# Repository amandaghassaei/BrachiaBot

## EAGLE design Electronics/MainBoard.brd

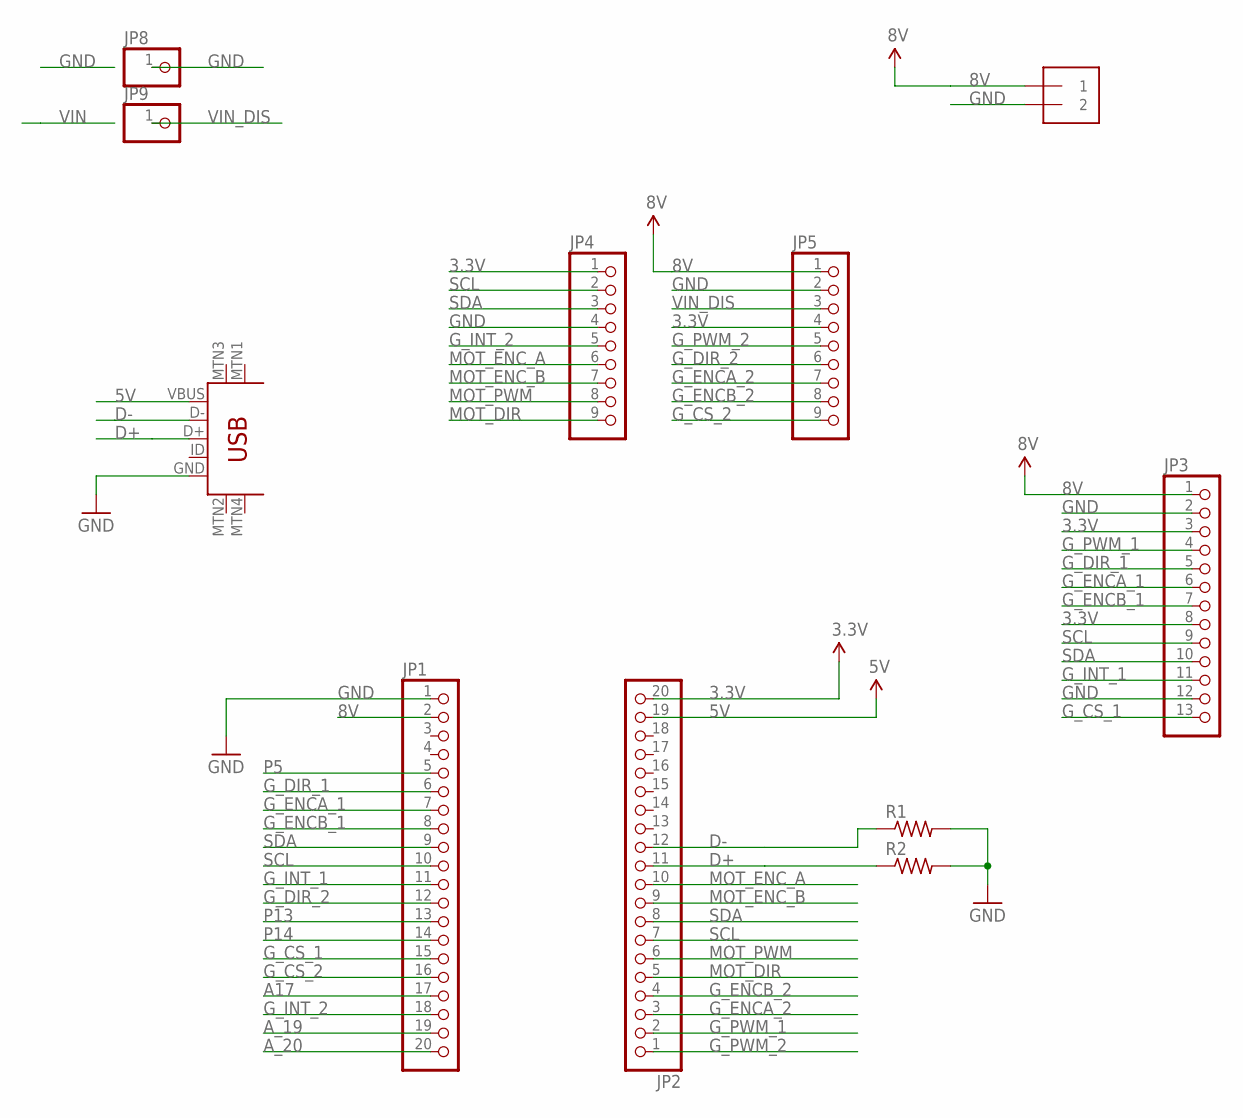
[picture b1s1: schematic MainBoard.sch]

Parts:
J1: 1X2-3.5MM
JP1, JP2: PINHD-1X20; 1X20
JP3: PINHD-1X13; 1X13
JP4, JP5: PINHD-1X9; 1X09-BIG
JP8, JP9: PINHD-1X1; 1X01
R1, R2: RES-US1206; R1206
U$1: USB-MINIB-5PIN; USB-MINIB

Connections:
3.3V: JP2.20, JP3.3, JP3.8, JP4.1, JP5.4
5V: JP2.19, U$1.VBUS
8V: J1.1, JP1.2, JP3.1, JP5.1
A17: JP1.17
A_19: JP1.19
A_20: JP1.20
D+: JP2.11, R2.1, U$1.D+
D-: JP2.12, R1.1, U$1.D-
GND: J1.2, JP1.1, JP3.2, JP3.12, JP4.4, JP5.2, JP8.1, R1.2, R2.2, U$1.GND
G_CS_1: JP1.15, JP3.13
G_CS_2: JP1.16, JP5.9
G_DIR_1: JP1.6, JP3.5
G_DIR_2: JP1.12, JP5.6
G_ENCA_1: JP1.7, JP3.6
G_ENCA_2: JP2.3, JP5.7
G_ENCB_1: JP1.8, JP3.7
G_ENCB_2: JP2.4, JP5.8
G_INT_1: JP1.11, JP3.11
G_INT_2: JP1.18, JP4.5
G_PWM_1: JP2.2, JP3.4
G_PWM_2: JP2.1, JP5.5
MOT_DIR: JP2.5, JP4.9
MOT_ENC_A: JP2.10, JP4.6
MOT_ENC_B: JP2.9, JP4.7
MOT_PWM: JP2.6, JP4.8
P5: JP1.5
P13: JP1.13
P14: JP1.14
SCL: JP1.10, JP2.7, JP3.9, JP4.2
SDA: JP1.9, JP2.8, JP3.10, JP4.3
VIN_DIS: JP5.3, JP9.1

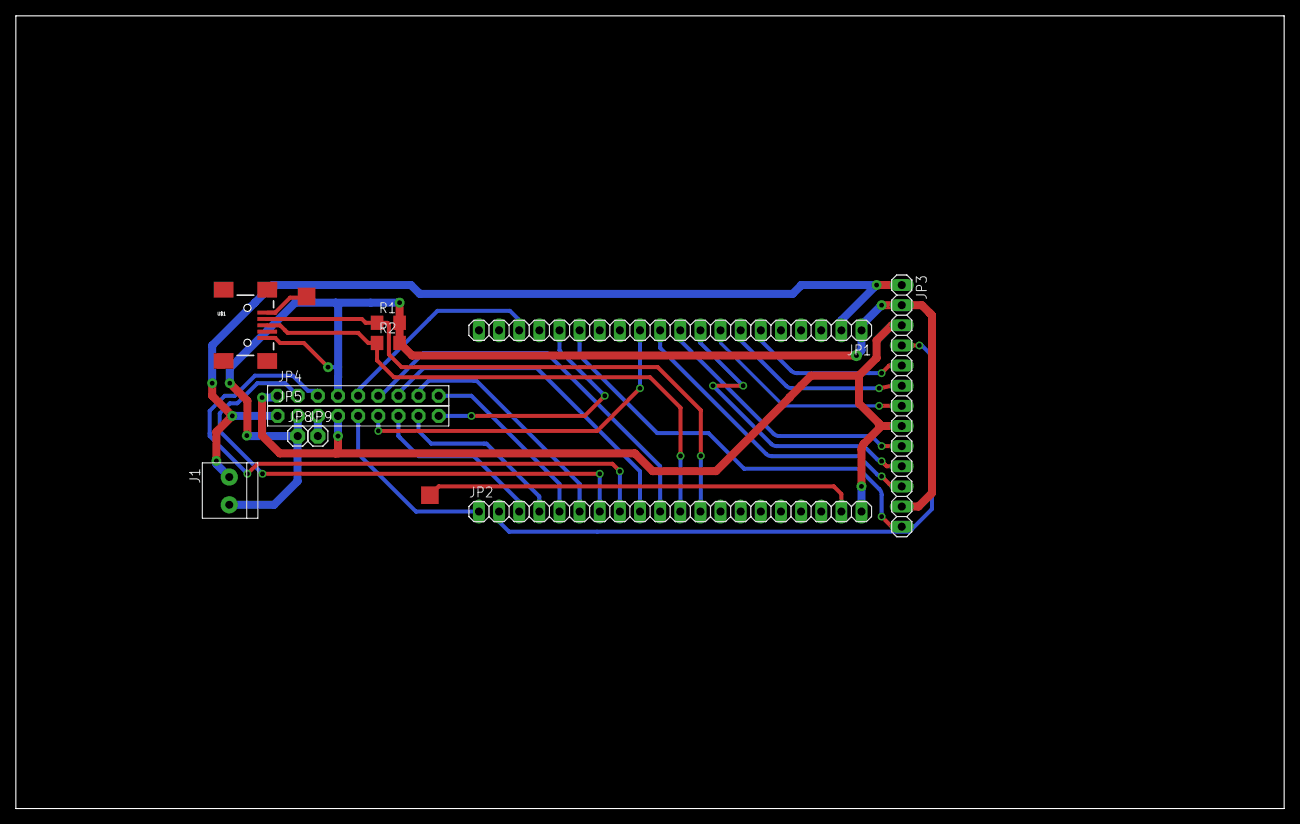
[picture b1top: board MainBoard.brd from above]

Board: 2 copper layers, 160.0 x 100.0 mm, 11 parts (0 on the bottom side), 25 nets.

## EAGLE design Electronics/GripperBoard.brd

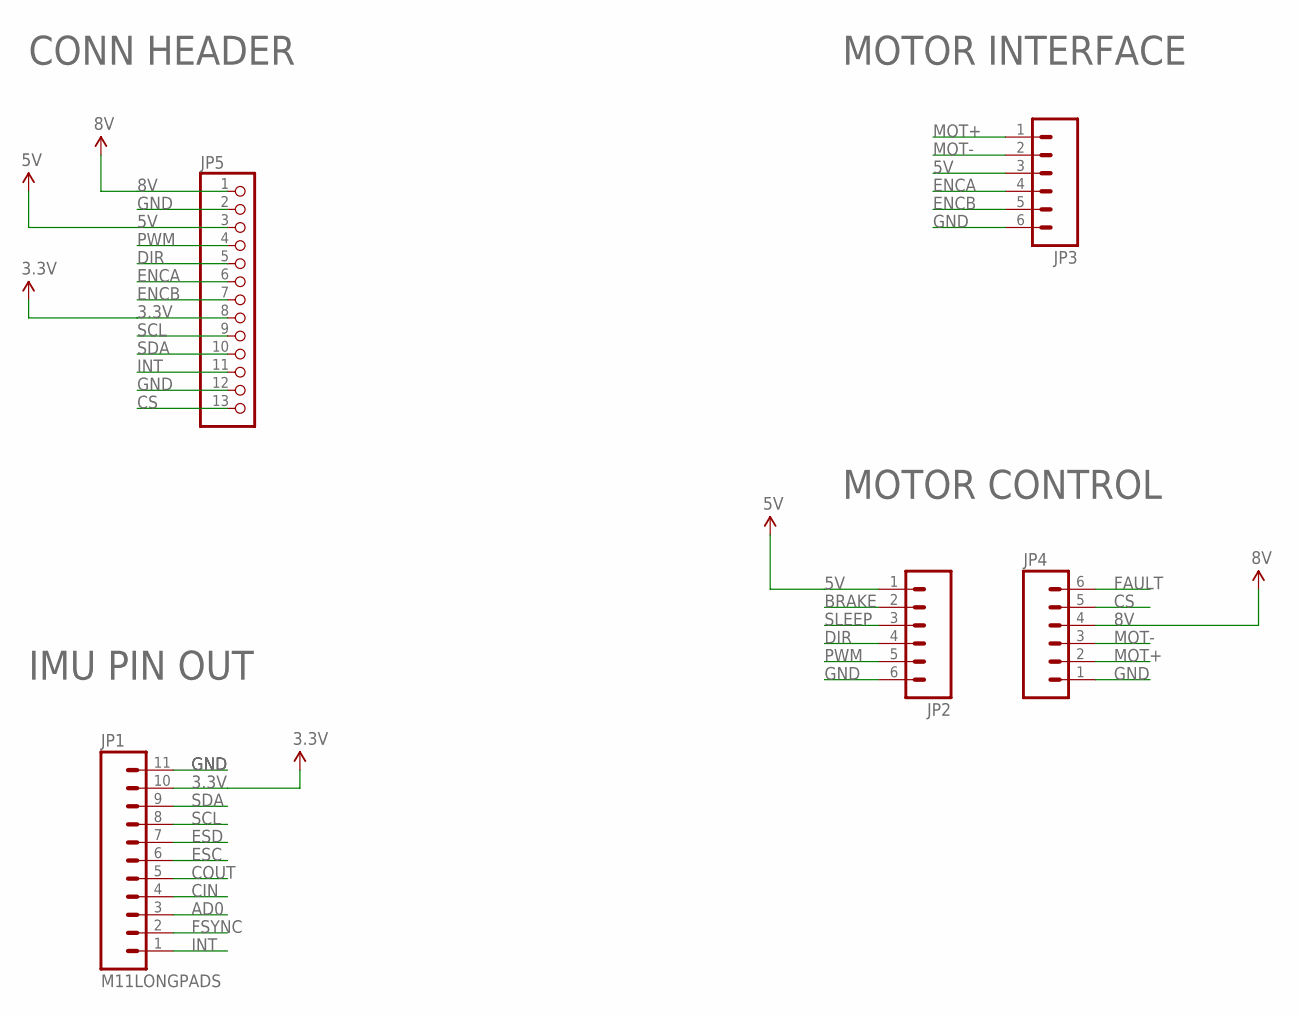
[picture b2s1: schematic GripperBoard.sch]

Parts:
JP1: M11LONGPADS; 1X11_LONGPADS
JP2, JP3, JP4: M06LONGPADS; 1X06_LONGPADS
JP5: PINHD-1X13; 1X13

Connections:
3.3V: JP1.10, JP5.8
5V: JP2.1, JP3.3, JP5.3
8V: JP4.4, JP5.1
AD0: JP1.3
BRAKE: JP2.2
CIN: JP1.4
COUT: JP1.5
CS: JP4.5, JP5.13
DIR: JP2.4, JP5.5
ENCA: JP3.4, JP5.6
ENCB: JP3.5, JP5.7
ESC: JP1.6
ESD: JP1.7
FAULT: JP4.6
FSYNC: JP1.2
GND: JP1.11, JP2.6, JP3.6, JP4.1, JP5.2, JP5.12
INT: JP1.1, JP5.11
MOT+: JP3.1, JP4.2
MOT-: JP3.2, JP4.3
PWM: JP2.5, JP5.4
SCL: JP1.8, JP5.9
SDA: JP1.9, JP5.10
SLEEP: JP2.3

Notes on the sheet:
MOTOR CONTROL
MOTOR INTERFACE
IMU PIN OUT
CONN HEADER

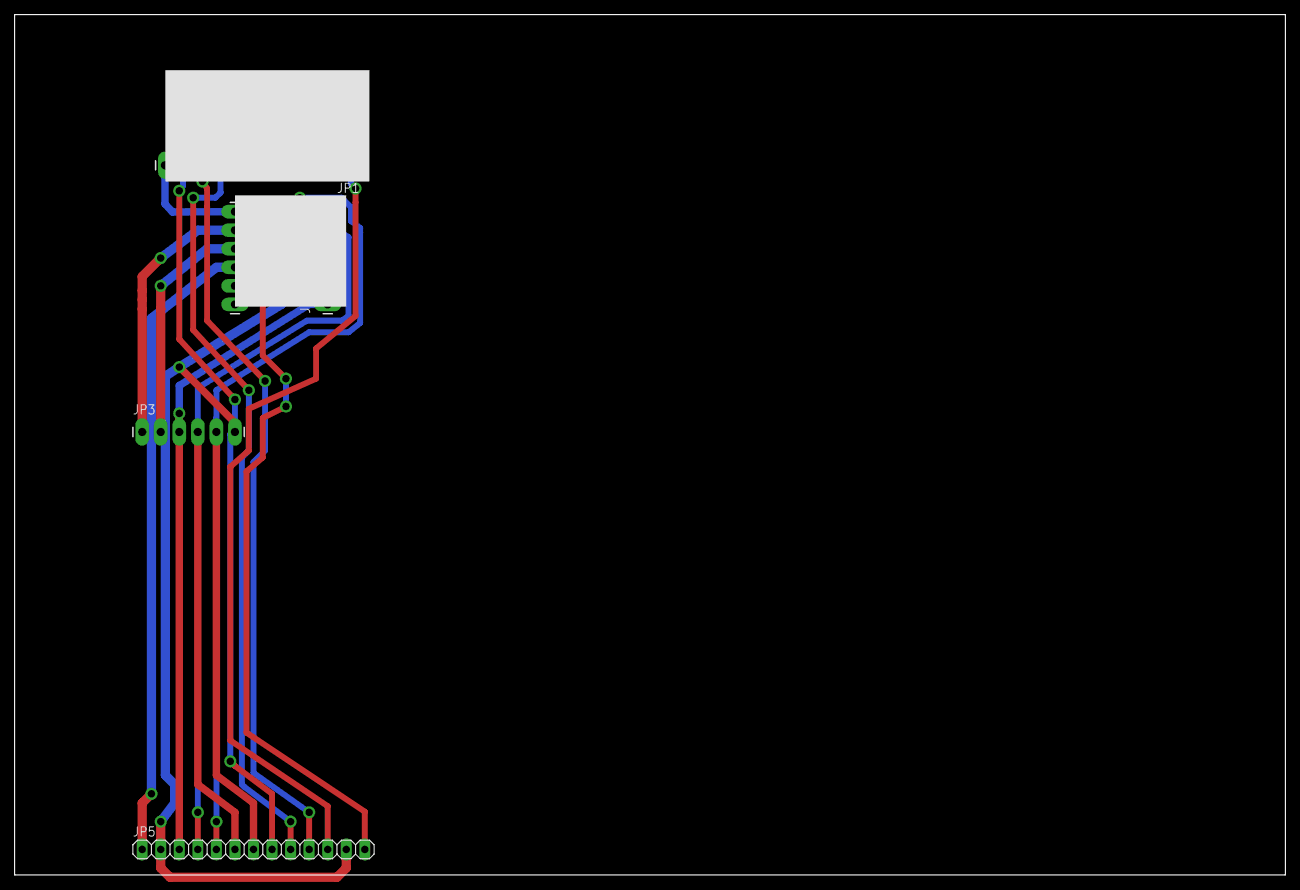
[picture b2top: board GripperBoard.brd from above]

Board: 2 copper layers, 174.0 x 117.8 mm, 5 parts (0 on the bottom side), 14 nets.

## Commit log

2015-10-05 double pendulum code
2015-10-05 renaming
2015-10-05 remove unnecessary vars
2015-10-05 triple pendulum
2015-10-05 quad pendulum
2015-10-05 optional fixed theta 2, theta 4
2015-10-05 comments
2015-10-05 dynamics in separate files
2015-10-05 comment
2015-10-05 organizatin
2015-10-05 lattice pitch
2015-10-05 params
2015-10-05 swinging and soft stops
2015-11-10 simplified back to two link pend
2015-11-10 shorter sim
2015-11-13 swing up nearly done
2015-11-13 small changes
2015-11-13 energy increasing dynamics look good
2015-11-14 happy with energy dynamics
2015-11-16 desired energy
2015-11-17 centrip compensation
2015-11-17 remove derived from version control
2015-11-17 ignore derived files
2015-11-17 map obstacle potentials on sim
2015-11-17 obstacle potential as a func of qs
2015-11-19 beginning to add optimization
2015-11-19 conitnuing to add opt code
2015-11-23 obstacle aboidance
2015-11-24 js rending started
2015-11-24 basic animation working
2015-11-24 gitignore
2015-11-24 serial comm
2015-11-24 ui hooked up to node server
2015-11-24 ui events firing
2015-11-24 get data from encoder
2015-11-28 adding controls code
2015-11-28 motor spinning
2015-11-28 dc motor control working
2015-11-28 weird behavior
2015-11-28 working on calibration
2015-11-28 calibration done
2015-11-29 main board eagle
2015-11-29 power routed
2015-11-29 half routed
2015-11-29 nearly done
2015-11-29 simulate theta1
2015-11-29 imu outpus valid json
2015-11-29 main board final layout v1
2015-12-01 mbed code
2015-12-01 main board edits
2015-12-01 serial monitor
2015-12-01 hide menu
2015-12-01 toggle graphs visibility
2015-12-01 init only one copy of serial monitor controller
2015-12-01 position data output
2015-12-03 delegate over sensor objects
2015-12-03 comm delegate
2015-12-03 serial monitor responsive
2015-12-03 mbed comm stack working
2015-12-03 board updates
2015-12-03 matlab swing up code added to mbed
2015-12-05 swing up starting to work
2015-12-06 sim edits to match spong
2015-12-06 targeting by setting theta2
2015-12-08 sim updates
2015-12-10 obstacle avoidance
2015-12-10 obstacle avoidance in opp direction
2015-12-10 some state of targeeting working
2015-12-10 fixes to targeting controller
2015-12-11 gain tuning
2015-12-11 swing up working
2015-12-11 simple targeting
2015-12-16 final code
2015-12-19 more realistic rendering
2015-12-19 case issue
2015-12-23 push script

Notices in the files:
parts and their libraries:
SparkFun: Licensing: CC v3.0 Share-Alike You are welcome to use this library for commercial purposes.
